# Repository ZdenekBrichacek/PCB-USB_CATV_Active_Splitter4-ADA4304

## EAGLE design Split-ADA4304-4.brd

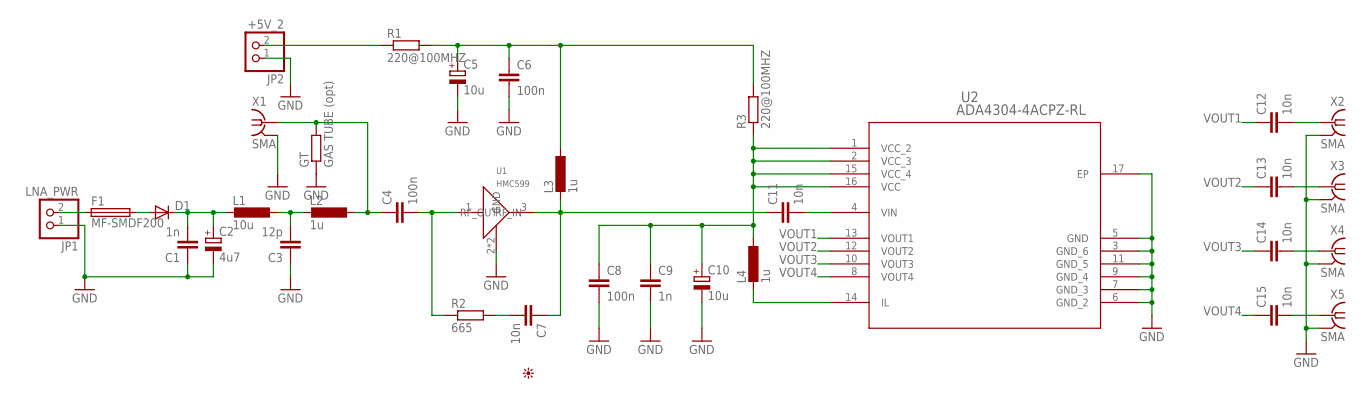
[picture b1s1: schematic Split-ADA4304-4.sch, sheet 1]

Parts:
C1, C9: 1n; C0603
C2: 4u7; SMC_A
C3: 12p; C0603
C4, C6, C8: 100n; C0603
C5, C10: 10u; SMC_A
C7, C11, C12, C13, C14, C15: 10n; C0603
D1: DIODE-MINIMELF; MINIMELF
F1: MF-SMDF200; MF-SMDF050
GT: GAS TUBE (opt); R0805
JP1: LNA_PWR; 1X02
JP2: +5V_2; 1X02
L1: 10u; L2012C
L2, L3, L4: 1u; L2012C
PICTO1: PICTO_1
R1, R3: 220@100MHZ; R0805
R2: 665; R0603
U1: HMC599; SOT89
U2: ADA4304-4ACPZ-RL; CP_16_2
X1, X2, X3, X4, X5: SMA; J502-ND-142-0701-801/806

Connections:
GND: C1.1, C2.-, C3.1, C5.-, C6.2, C8.2, C9.2, C10.-, GT.1, JP1.1, JP2.1, U1.2 (GND), U1.2.1 (GND), U2.3 (GND_6), U2.5 (GND), U2.6 (GND_2), U2.7 (GND_3), U2.9 (GND_4), U2.11 (GND_5), U2.17 (EP), X1.G@1 (2), X1.G@2 (2), X1.G@3 (2), X1.G@4 (2), X2.G@1 (2), X2.G@2 (2), X2.G@3 (2), X2.G@4 (2), X3.G@1 (2), X3.G@2 (2), X3.G@3 (2), X3.G@4 (2), X4.G@1 (2), X4.G@2 (2), X4.G@3 (2), X4.G@4 (2), X5.G@1 (2), X5.G@2 (2), X5.G@3 (2), X5.G@4 (2); also elsewhere on the board
unnamed: C8.1, C9.1, C10.+, L4.1, R3.1, U2.1 (VCC_2), U2.2 (VCC_3), U2.15 (VCC_4), U2.16 (VCC)
unnamed: F1.1, JP1.2
unnamed: C12.2, X2.1
unnamed: C13.2, X3.1
unnamed: C14.2, X4.1
unnamed: C4.1, GT.2, L2.1, X1.1
unnamed: C11.2, U2.4 (VIN)
unnamed: L4.2, U2.14 (IL)
unnamed: C15.2, X5.1
unnamed: C5.+, C6.1, L3.1, R1.2, R3.2
unnamed: C4.2, R2.1, U1.1 (RF_IN)
unnamed: JP2.2, R1.1
unnamed: C1.2, C2.+, D1.C, L1.2
unnamed: C3.2, L1.1, L2.2
unnamed: D1.A, F1.2
unnamed: C7.2, R2.2
RF_OUT: C7.1, C11.1, L3.2, U1.3 (RF_OUT)
VOUT1: C12.1, U2.13 (VOUT1)
VOUT2: C13.1, U2.12 (VOUT2)
VOUT3: C14.1, U2.10 (VOUT3)
VOUT4: C15.1, U2.8 (VOUT4)

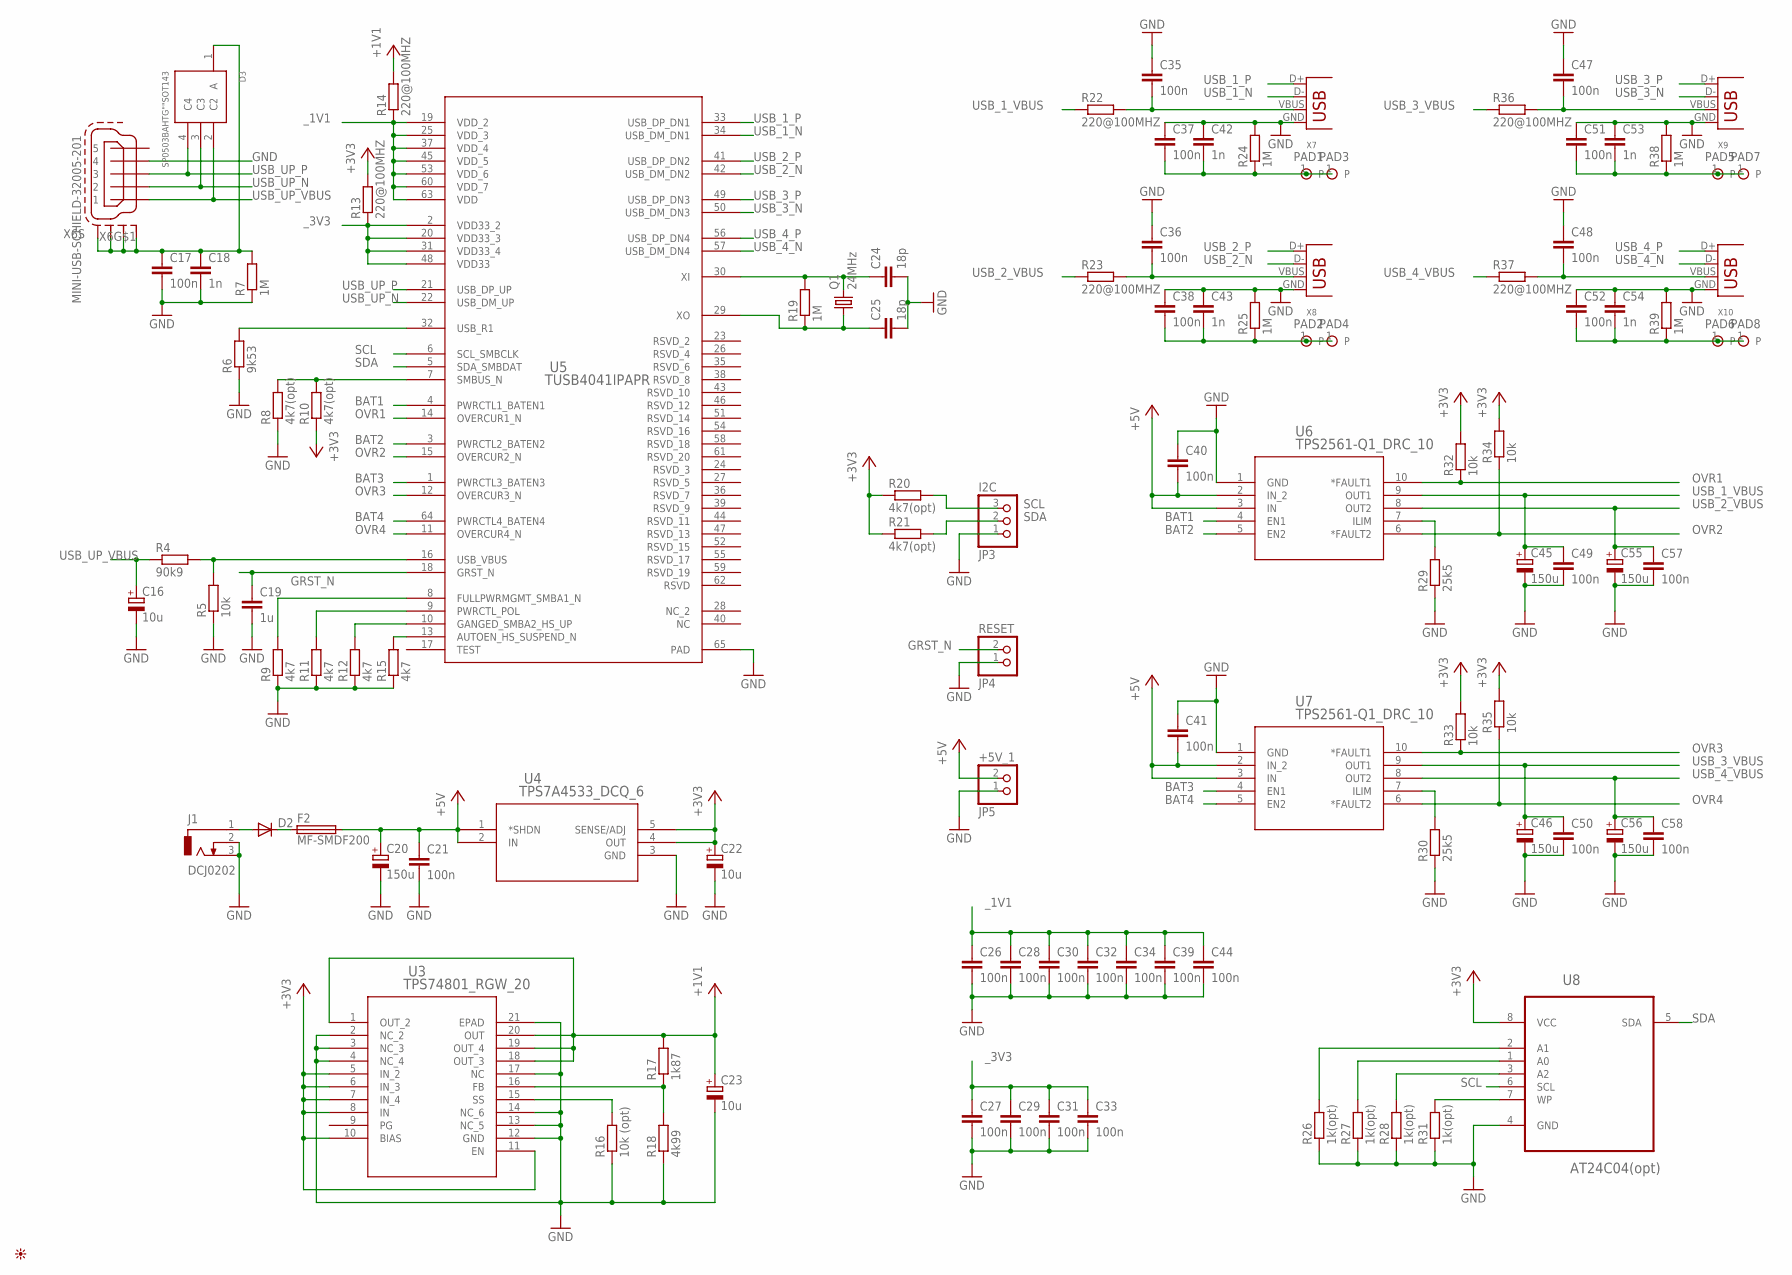
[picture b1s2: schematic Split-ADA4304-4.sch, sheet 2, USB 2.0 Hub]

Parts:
C16, C22, C23: 10u; SMC_B
C17, C21, C26, C27, C28, C29, C30, C31, C32, C33, C34, C35, C36, C37, C38, C39, C40, C41, C44, C47, C48, C49, C50, C51, C52, C57, C58: 100n; C0603
C18, C42, C43, C53, C54: 1n; C0603
C19: 1u; C1206
C20, C45, C46, C55, C56: 150u; E2,5-7
C24, C25: 18p; C0603
D2: DIODE-MINIMELF; MINIMELF
D3: SP0503BAHTG""SOT143; SOT143
F2: MF-SMDF200; MF-SMDF050
J1: DCJ0202
JP3: I2C; 1X03
JP4: RESET; 1X02
JP5: +5V_1; 1X02
PAD1, PAD2, PAD3, PAD4, PAD5, PAD6, PAD7, PAD8: PADPAD1.5; PAD1.5
PICTO2: PICTO_1
Q1: 24MHz; HC49UP
R4: 90k9; R0603
R5, R32, R33, R34, R35: 10k; R0603
R6: 9k53; R0603
R7, R19, R24, R25, R38, R39: 1M; R0603
R8, R10, R20, R21: 4k7(opt); R0603
R9, R11, R12, R15: 4k7; R0603
R13, R14, R22, R23, R36, R37: 220@100MHZ; R0805
R16: 10k (opt); R0603
R17: 1k87; R0603
R18: 4k99; R0603
R26, R27, R28, R31: 1k(opt); R0603
R29, R30: 25k5; R0603
U3: TPS74801_RGW_20; RGW20_3P15X3P15
U4: TPS7A4533_DCQ_6; DCQ6
U5: TUSB4041IPAPR; PAP0064K_N
U6, U7: TPS2561-Q1_DRC_10; DRC10_2P4X1P65
U8: AT24C04(opt); SOIC127P600X175-8N
X6: MINI-USB-SCHIELD-32005-201; 32005-201
X7, X8, X9, X10: USB-A-HU

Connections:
+3V3: C22.+, R10.1, R13.2, R20.1, R21.1, R32.2, R33.2, R34.2, R35.2, U3.5 (IN_2), U3.6 (IN_3), U3.7 (IN_4), U3.8 (IN), U3.10 (BIAS), U3.11 (EN), U4.4 (OUT), U4.5 (SENSE/ADJ), U8.8 (VCC)
+5V: C20.+, C21.1, C40.2, C41.2, F2.2, JP5.2, U4.1 (*SHDN), U4.2 (IN), U6.2 (IN_2), U6.3 (IN), U7.2 (IN_2), U7.3 (IN)
BAT1: U5.4 (PWRCTL1_BATEN1), U6.4 (EN1)
BAT2: U5.3 (PWRCTL2_BATEN2), U6.5 (EN2)
BAT3: U5.1 (PWRCTL3_BATEN3), U7.4 (EN1)
BAT4: U5.64 (PWRCTL4_BATEN4), U7.5 (EN2)
GND: C16.-, C17.2, C18.2, C19.2, C20.-, C21.2, C22.-, C23.-, C24.2, C25.2, C26.2, C27.2, C28.2, C29.2, C30.2, C31.2, C32.2, C33.2, C34.2, C35.1, C36.1, C37.1, C38.1, C39.2, C40.1, C41.1, C42.1, C43.1, C44.2, C45.-, C46.-, C47.1, C48.1, C49.2, C50.2, C51.1, C52.1, C53.1, C54.1, C55.-, C56.-, C57.2, C58.2, J1.2, J1.3, JP3.1, JP4.1, JP5.1, R5.1, R6.1, R7.1, R8.1, R9.1, R11.1, R12.1, R15.1, R16.1, R18.1, R24.2, R25.2, R26.1, R27.1, R28.1, R29.1, R30.1, R31.1, R38.2, R39.2, U3.2 (NC_2), U3.3 (NC_3), U3.4 (NC_4), U3.12 (GND), U3.13 (NC_5), U3.14 (NC_6), U3.17 (NC), U3.21 (EPAD), U4.3 (GND), U5.65 (PAD), U6.1 (GND), U7.1 (GND), U8.4 (GND), X6.4, X7.GND, X8.GND, X9.GND, X10.GND; also elsewhere on the board
GRST_N: C19.1, JP4.2, U5.18 (GRST_N)
unnamed: C24.1, Q1.2, R19.2, U5.30 (XI)
unnamed: C25.1, Q1.1, R19.1, U5.29 (XO)
unnamed: R4.2, R5.2, U5.16 (USB_VBUS)
unnamed: R6.2, U5.32 (USB_R1)
unnamed: R11.2, U5.9 (PWRCTL_POL)
unnamed: R9.2, U5.8 (FULLPWRMGMT_SMBA1_N)
unnamed: R8.2, R10.2, U5.7 (SMBUS_N)
unnamed: R12.2, U5.10 (GANGED_SMBA2_HS_UP)
unnamed: R15.2, U5.13 (AUTOEN_HS_SUSPEND_N)
unnamed: C37.2, C42.2, PAD1.1, PAD3.1, R24.1
unnamed: C35.2, R22.2, X7.VBUS
unnamed: C38.2, C43.2, PAD2.1, PAD4.1, R25.1
unnamed: C36.2, R23.2, X8.VBUS
unnamed: C51.2, C53.2, PAD5.1, PAD7.1, R38.1
unnamed: C47.2, R36.2, X9.VBUS
unnamed: C52.2, C54.2, PAD6.1, PAD8.1, R39.1
unnamed: C48.2, R37.2, X10.VBUS
unnamed: R17.1, R18.2, U3.16 (FB)
unnamed: R16.2, U3.15 (SS)
unnamed: D2.A, J1.1
unnamed: R29.2, U6.7 (ILIM)
unnamed: R30.2, U7.7 (ILIM)
unnamed: R31.2, U8.7 (WP)
unnamed: R28.2, U8.3 (A2)
unnamed: R27.2, U8.1 (A0)
unnamed: R26.2, U8.2 (A1)
unnamed: D2.C, F2.1
unnamed: C17.1, C18.1, D3.1 (A), R7.2, X6.M1 (S1), X6.M2 (S2), X6.M3 (S3), X6.M4 (S4)
OVR1: R32.1, U5.14 (OVERCUR1_N), U6.10 (*FAULT1)
OVR2: R34.1, U5.15 (OVERCUR2_N), U6.6 (*FAULT2)
OVR3: R33.1, U5.12 (OVERCUR3_N), U7.10 (*FAULT1)
OVR4: R35.1, U5.11 (OVERCUR4_N), U7.6 (*FAULT2)
SCL: JP3.3, R20.2, U5.6 (SCL_SMBCLK), U8.6 (SCL)
SDA: JP3.2, R21.2, U5.5 (SDA_SMBDAT), U8.5 (SDA)
USB_1_N: U5.34 (USB_DM_DN1), X7.D-
USB_1_P: U5.33 (USB_DP_DN1), X7.D+
USB_1_VBUS: C45.+, C49.1, R22.1, U6.9 (OUT1)
USB_2_N: U5.42 (USB_DM_DN2), X8.D-
USB_2_P: U5.41 (USB_DP_DN2), X8.D+
USB_2_VBUS: C55.+, C57.1, R23.1, U6.8 (OUT2)
USB_3_N: U5.50 (USB_DM_DN3), X9.D-
USB_3_P: U5.49 (USB_DP_DN3), X9.D+
USB_3_VBUS: C46.+, C50.1, R36.1, U7.9 (OUT1)
USB_4_N: U5.57 (USB_DM_DN4), X10.D-
USB_4_P: U5.56 (USB_DP_DN4), X10.D+
USB_4_VBUS: C56.+, C58.1, R37.1, U7.8 (OUT2)
USB_UP_N: D3.3 (C3), U5.22 (USB_DM_UP), X6.2
USB_UP_P: D3.4 (C4), U5.21 (USB_DP_UP), X6.3
USB_UP_VBUS: C16.+, D3.2 (C2), R4.1, X6.1
VCC: C23.+, R14.2, R17.2, U3.1 (OUT_2), U3.18 (OUT_3), U3.19 (OUT_4), U3.20 (OUT)
_1V1: C26.1, C28.1, C30.1, C32.1, C34.1, C39.1, C44.1, R14.1, U5.19 (VDD_2), U5.25 (VDD_3), U5.37 (VDD_4), U5.45 (VDD_5), U5.53 (VDD_6), U5.60 (VDD_7), U5.63 (VDD)
_3V3: C27.1, C29.1, C31.1, C33.1, R13.1, U5.2 (VDD33_2), U5.20 (VDD33_3), U5.31 (VDD33_4), U5.48 (VDD33)

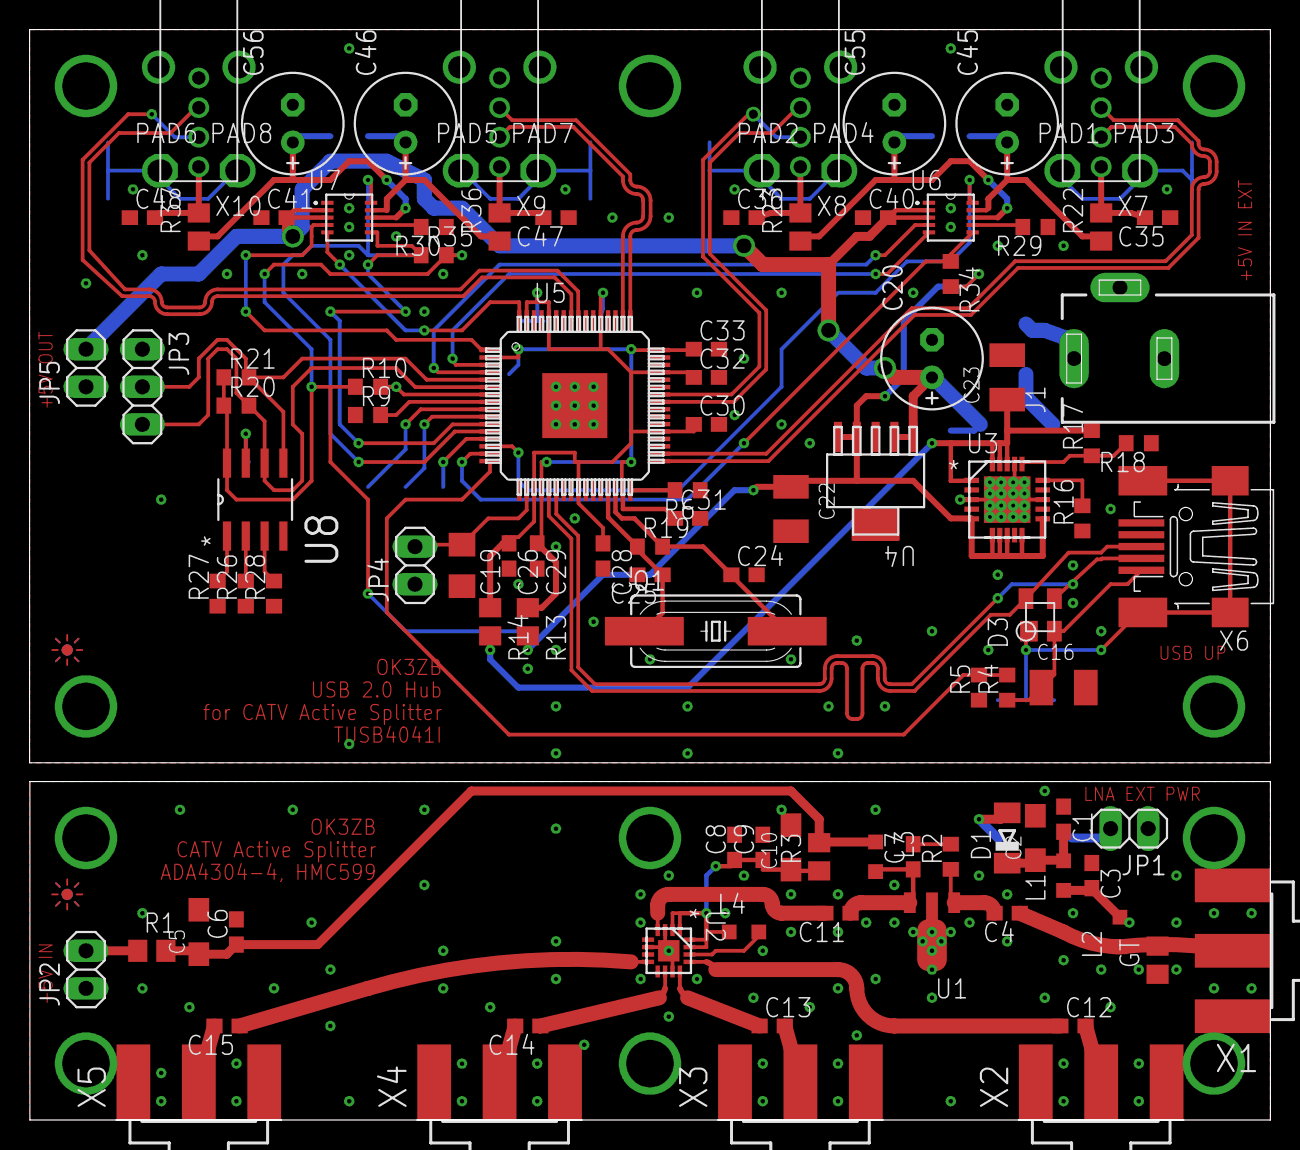
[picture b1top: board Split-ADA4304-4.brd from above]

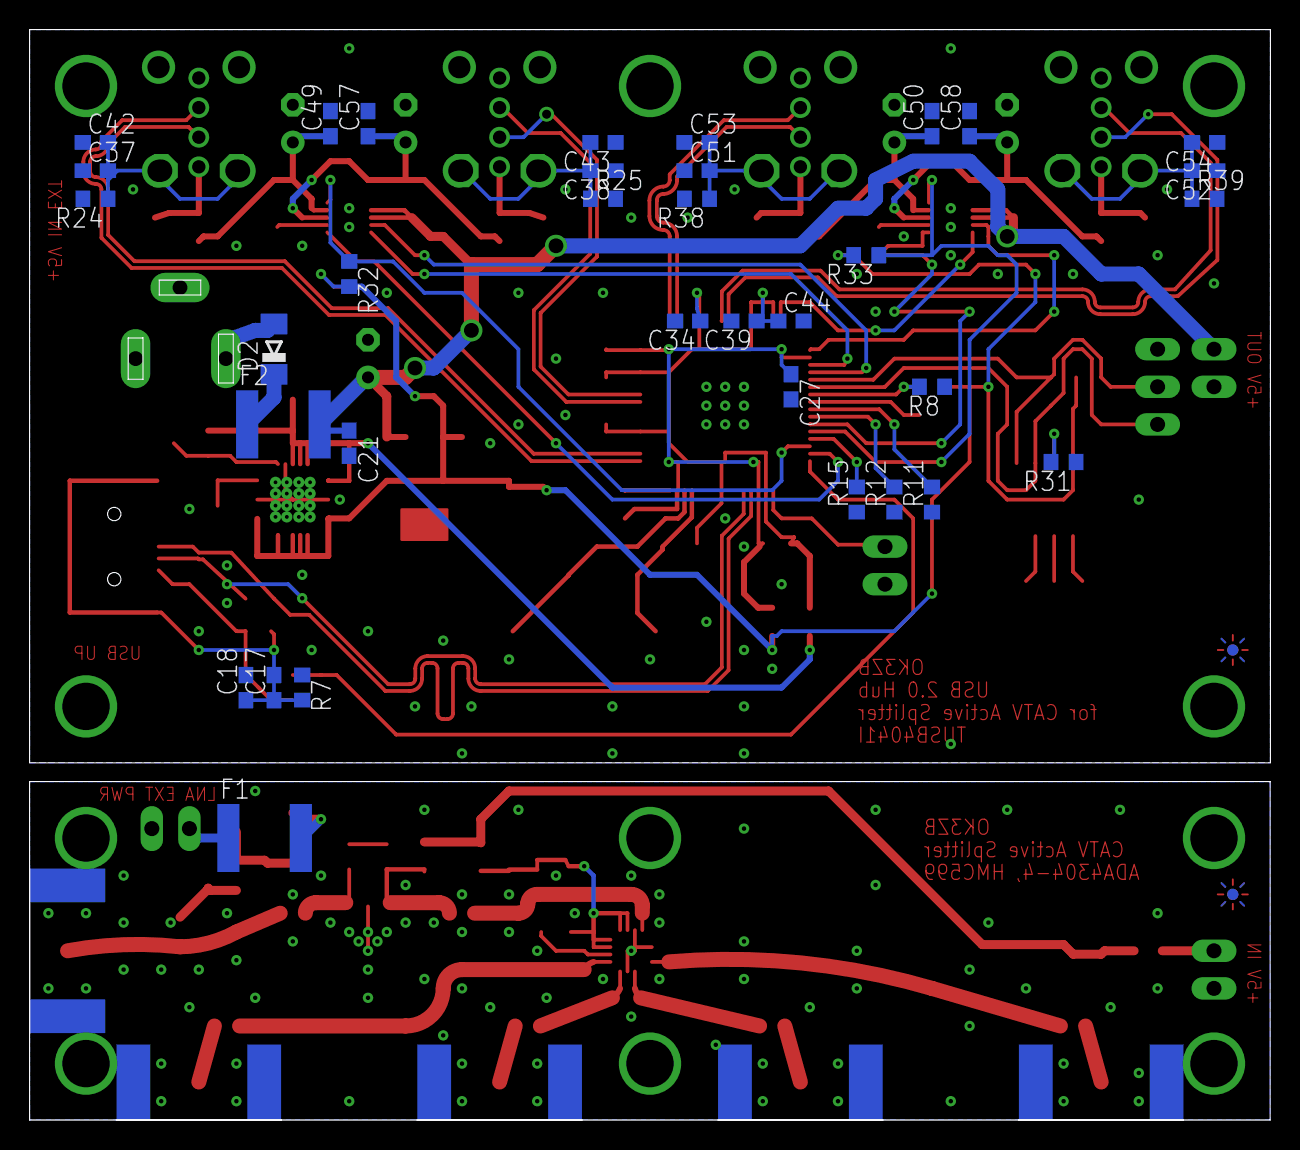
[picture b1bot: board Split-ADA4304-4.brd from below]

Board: 2 copper layers, 83.8 x 73.7 mm, 142 parts (34 on the bottom side), 81 nets.

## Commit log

2017-10-10 :tada: Added .gitattributes & .gitignore files
2017-10-10 Initial version
2017-10-10 Update schema pictures
